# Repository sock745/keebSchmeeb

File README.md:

https://cad.onshape.com/documents/5618978a45e60a072225bb33/w/fbe41e280935ff233e73254a/e/3686d4072979cc3bd81b8073?renderMode=0&uiState=66bd86b7268c9927061f2a9d

ONBOARD GRANT INFO -

Alex Wang
slack_handle: Alex Wang
github_handle: sock745
---

Custom 65% Keyboard Design w/ Rotary Encoder Knob

Standard keyboard matrix that I plan to solder a ProMicro as the microcontroller and an EC-11 rotary encoder for a volume knob.

COST ETA

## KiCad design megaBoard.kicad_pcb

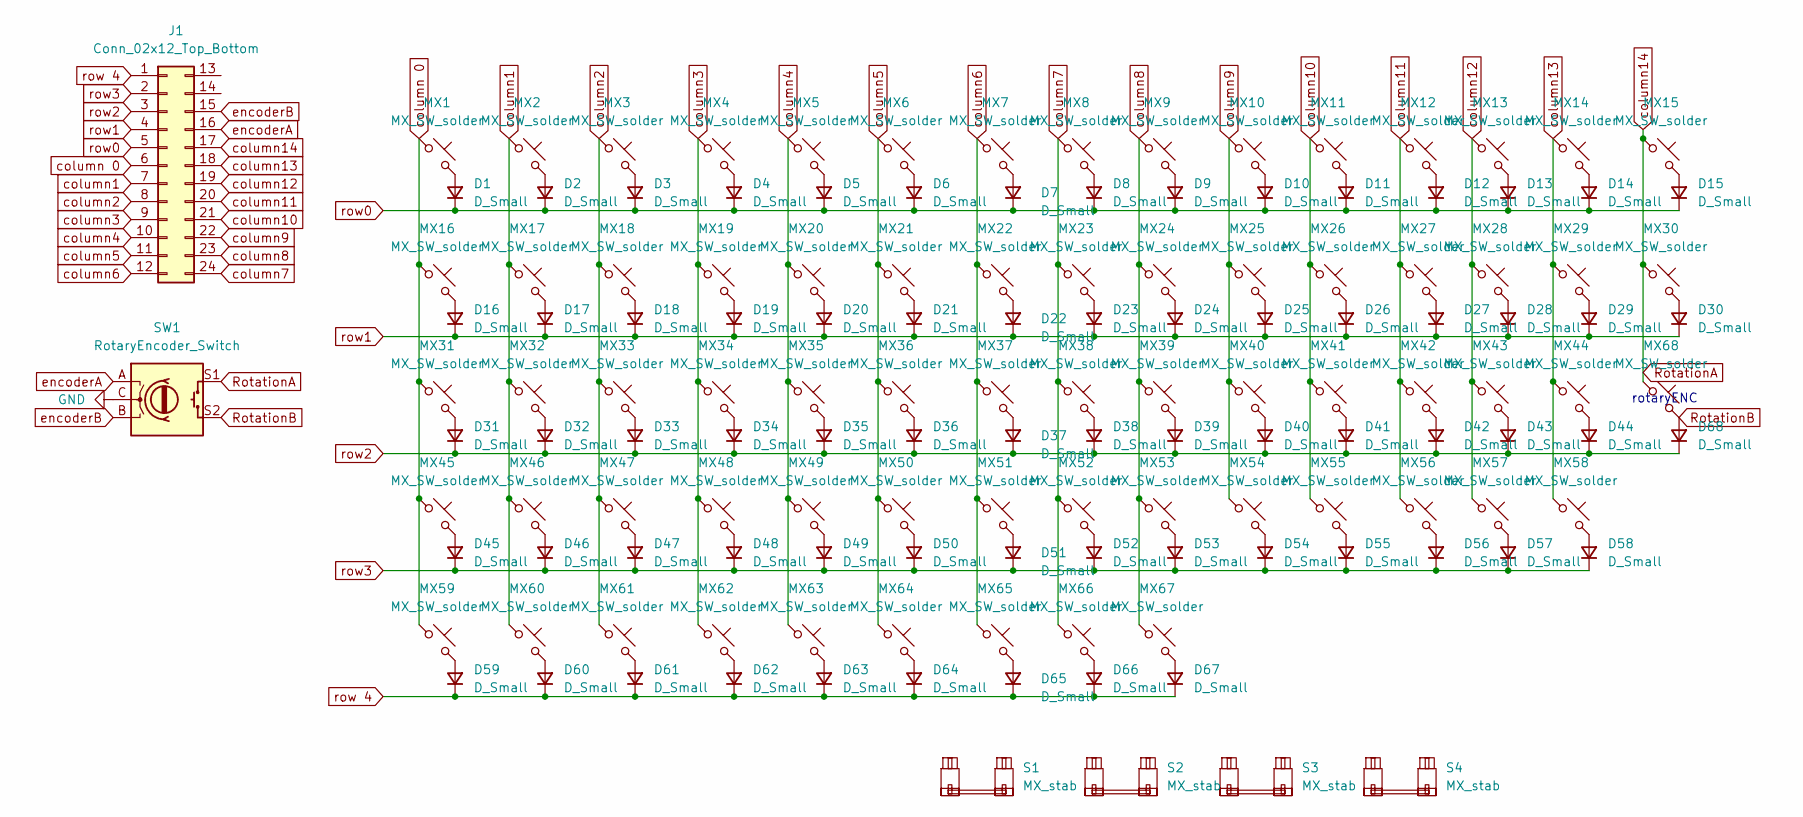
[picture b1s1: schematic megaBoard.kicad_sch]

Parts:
D1, D2, D3, D4, D5, D6, D7, D8, D9, D10, D11, D12, D13, D14, D15, D16, D17, D18, D19, D20, D21, D22, D23, D24, D25, D26, D27, D28, D29, D30, D31, D32, D33, D34, D35, D36, D37, D38, D39, D40, D41, D42, D43, D44, D45, D46, D47, D48, D49, D50, D51, D52, D53, D54, D55, D56, D57, D58, D59, D60, D61, D62, D63, D64, D65, D66, D67, D68: D_Small; D_SOD-123
J1: Conn_02x12_Top_Bottom; ProMicro_USBdn
MX1, MX2, MX3, MX4, MX5, MX6, MX7, MX8, MX9, MX10, MX11, MX12, MX13, MX14, MX15, MX17, MX18, MX19, MX20, MX21, MX22, MX23, MX24, MX25, MX26, MX27, MX28, MX30, MX32, MX33, MX34, MX35, MX36, MX37, MX38, MX39, MX40, MX41, MX42, MX43, MX44, MX45, MX46, MX47, MX48, MX49, MX50, MX51, MX52, MX53, MX54, MX55, MX57, MX58, MX62, MX65, MX66, MX67, MX68: MX_SW_solder; SW_MX_HS_CPG151101S11_1u
MX16, MX29: MX_SW_solder; SW_MX_HS_CPG151101S11_1.5u
MX31, MX59, MX60, MX61, MX63, MX64: MX_SW_solder; SW_MX_HS_CPG151101S11_1.25u
MX56: MX_SW_solder; SW_MX_HS_CPG151101S11_1.75u
S1: MX_stab; STAB_MX_P_2u
S2, S3: MX_stab; STAB_MX_P_2.25u
S4: MX_stab; STAB_MX_P_6.25u
SW1: RotaryEncoder_Switch; RotaryEncoder_EC11

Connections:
GND: SW1.C
unnamed: D1.2 (A), MX1.2
unnamed: D2.2 (A), MX2.2
unnamed: D3.2 (A), MX3.2
unnamed: D4.2 (A), MX4.2
unnamed: D5.2 (A), MX5.2
unnamed: D6.2 (A), MX6.2
unnamed: D7.2 (A), MX7.2
unnamed: D8.2 (A), MX8.2
unnamed: D9.2 (A), MX9.2
unnamed: D10.2 (A), MX10.2
unnamed: D11.2 (A), MX11.2
unnamed: D12.2 (A), MX12.2
unnamed: D13.2 (A), MX13.2
unnamed: D14.2 (A), MX14.2
unnamed: D15.2 (A), MX15.2
unnamed: D16.2 (A), MX16.2
unnamed: D17.2 (A), MX17.2
unnamed: D18.2 (A), MX18.2
unnamed: D19.2 (A), MX19.2
unnamed: D20.2 (A), MX20.2
unnamed: D21.2 (A), MX21.2
unnamed: D22.2 (A), MX22.2
unnamed: D23.2 (A), MX23.2
unnamed: D24.2 (A), MX24.2
unnamed: D25.2 (A), MX25.2
unnamed: D26.2 (A), MX26.2
unnamed: D27.2 (A), MX27.2
unnamed: D28.2 (A), MX28.2
unnamed: D29.2 (A), MX29.2
unnamed: D30.2 (A), MX30.2
unnamed: D31.2 (A), MX31.2
unnamed: D32.2 (A), MX32.2
unnamed: D33.2 (A), MX33.2
unnamed: D34.2 (A), MX34.2
unnamed: D35.2 (A), MX35.2
unnamed: D36.2 (A), MX36.2
unnamed: D37.2 (A), MX37.2
unnamed: D38.2 (A), MX38.2
unnamed: D39.2 (A), MX39.2
unnamed: D40.2 (A), MX40.2
unnamed: D41.2 (A), MX41.2
unnamed: D42.2 (A), MX42.2
unnamed: D43.2 (A), MX43.2
unnamed: D44.2 (A), MX44.2
unnamed: D45.2 (A), MX45.2
unnamed: D46.2 (A), MX46.2
unnamed: D47.2 (A), MX47.2
unnamed: D48.2 (A), MX48.2
unnamed: D49.2 (A), MX49.2
unnamed: D50.2 (A), MX50.2
unnamed: D51.2 (A), MX51.2
unnamed: D52.2 (A), MX52.2
unnamed: D53.2 (A), MX53.2
unnamed: D54.2 (A), MX54.2
unnamed: D55.2 (A), MX55.2
unnamed: D56.2 (A), MX56.2
unnamed: D57.2 (A), MX57.2
unnamed: D58.2 (A), MX58.2
unnamed: D59.2 (A), MX59.2
unnamed: D60.2 (A), MX60.2
unnamed: D61.2 (A), MX61.2
unnamed: D62.2 (A), MX62.2
unnamed: D63.2 (A), MX63.2
unnamed: D64.2 (A), MX64.2
unnamed: D65.2 (A), MX65.2
unnamed: D66.2 (A), MX66.2
unnamed: D67.2 (A), MX67.2
RotationA: J1.17, MX15.1, MX30.1, MX68.1, SW1.S1
RotationB: D68.2 (A), MX68.2, SW1.S2
column1: J1.7, MX2.1, MX17.1, MX32.1, MX46.1, MX60.1
column2: J1.8, MX3.1, MX18.1, MX33.1, MX47.1, MX61.1
column3: J1.9, MX4.1, MX19.1, MX34.1, MX48.1, MX62.1
column4: J1.10, MX5.1, MX20.1, MX35.1, MX49.1, MX63.1
column5: J1.11, MX6.1, MX21.1, MX36.1, MX50.1, MX64.1
column6: J1.12, MX7.1, MX22.1, MX37.1, MX51.1, MX65.1
column7: J1.24, MX8.1, MX23.1, MX38.1, MX52.1, MX66.1
column8: J1.23, MX9.1, MX24.1, MX39.1, MX53.1, MX67.1
column9: J1.22, MX10.1, MX25.1, MX40.1, MX54.1
column10: J1.21, MX11.1, MX26.1, MX41.1, MX55.1
column11: J1.20, MX12.1, MX27.1, MX42.1, MX56.1
column12: J1.19, MX13.1, MX28.1, MX43.1, MX57.1
column13: J1.18, MX14.1, MX29.1, MX44.1, MX58.1
column 0: J1.6, MX1.1, MX16.1, MX31.1, MX45.1, MX59.1
encoderA: J1.16, SW1.A
encoderB: J1.15, SW1.B
row0: D1.1 (K), D2.1 (K), D3.1 (K), D4.1 (K), D5.1 (K), D6.1 (K), D7.1 (K), D8.1 (K), D9.1 (K), D10.1 (K), D11.1 (K), D12.1 (K), D13.1 (K), D14.1 (K), D15.1 (K), J1.5
row1: D16.1 (K), D17.1 (K), D18.1 (K), D19.1 (K), D20.1 (K), D21.1 (K), D22.1 (K), D23.1 (K), D24.1 (K), D25.1 (K), D26.1 (K), D27.1 (K), D28.1 (K), D29.1 (K), D30.1 (K), J1.4
row2: D31.1 (K), D32.1 (K), D33.1 (K), D34.1 (K), D35.1 (K), D36.1 (K), D37.1 (K), D38.1 (K), D39.1 (K), D40.1 (K), D41.1 (K), D42.1 (K), D43.1 (K), D44.1 (K), D68.1 (K), J1.3
row3: D45.1 (K), D46.1 (K), D47.1 (K), D48.1 (K), D49.1 (K), D50.1 (K), D51.1 (K), D52.1 (K), D53.1 (K), D54.1 (K), D55.1 (K), D56.1 (K), D57.1 (K), D58.1 (K), J1.2
row 4: D59.1 (K), D60.1 (K), D61.1 (K), D62.1 (K), D63.1 (K), D64.1 (K), D65.1 (K), D66.1 (K), D67.1 (K), J1.1

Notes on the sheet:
rotaryENC

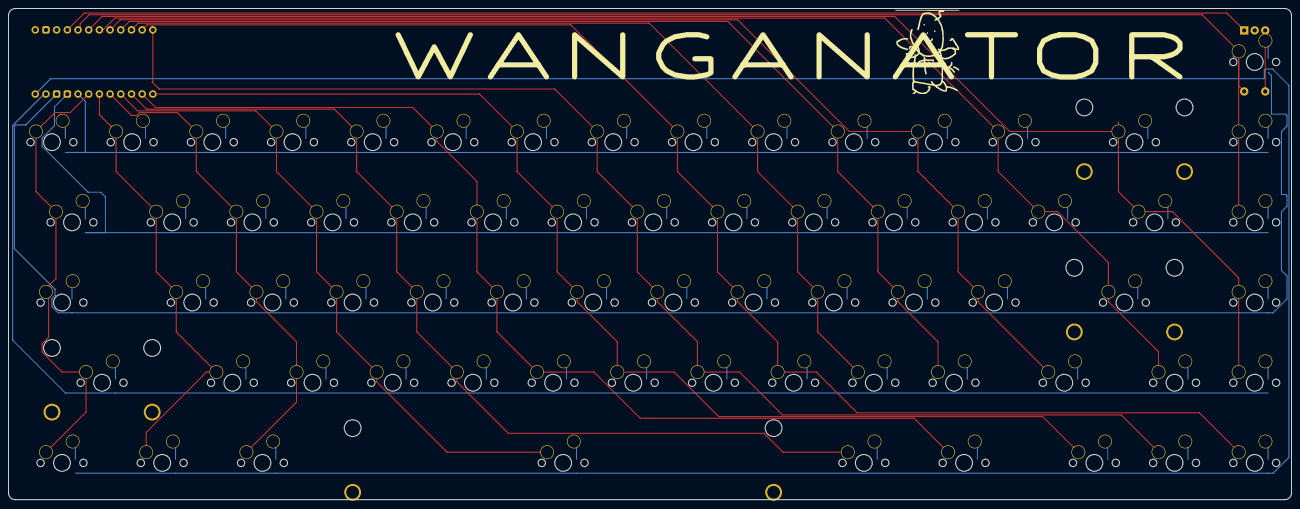
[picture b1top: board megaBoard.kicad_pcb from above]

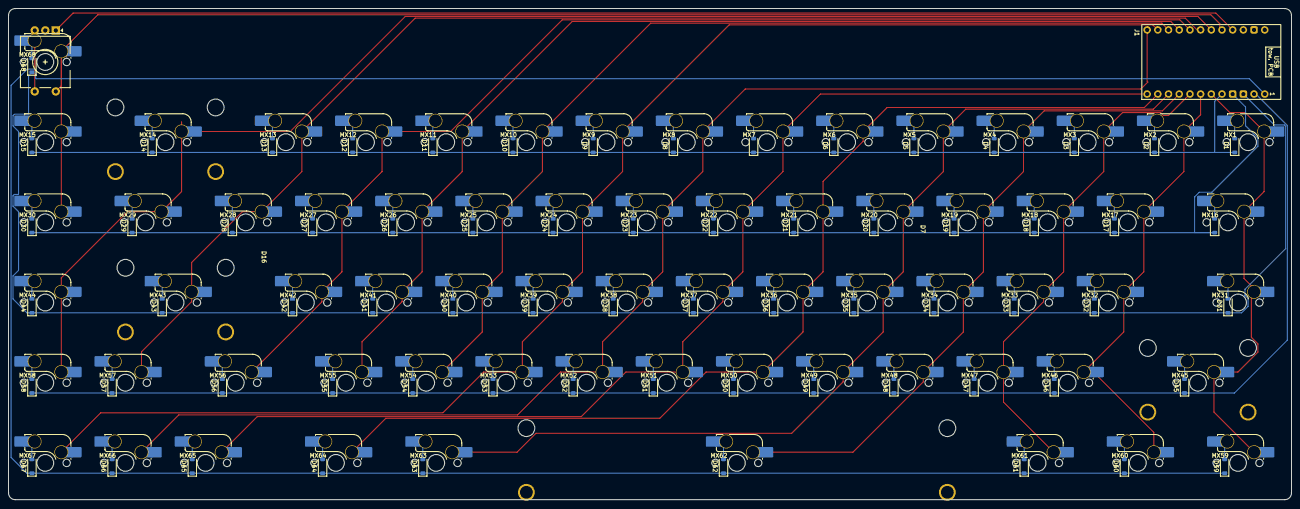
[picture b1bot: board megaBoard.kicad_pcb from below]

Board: 2 copper layers, 304.8 x 116.7 mm, 142 parts (138 on the bottom side), 90 nets.

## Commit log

2024-08-07 Create scrapbook
2024-08-07 Create Screenshot
2024-08-15 Create OnshapeLink
